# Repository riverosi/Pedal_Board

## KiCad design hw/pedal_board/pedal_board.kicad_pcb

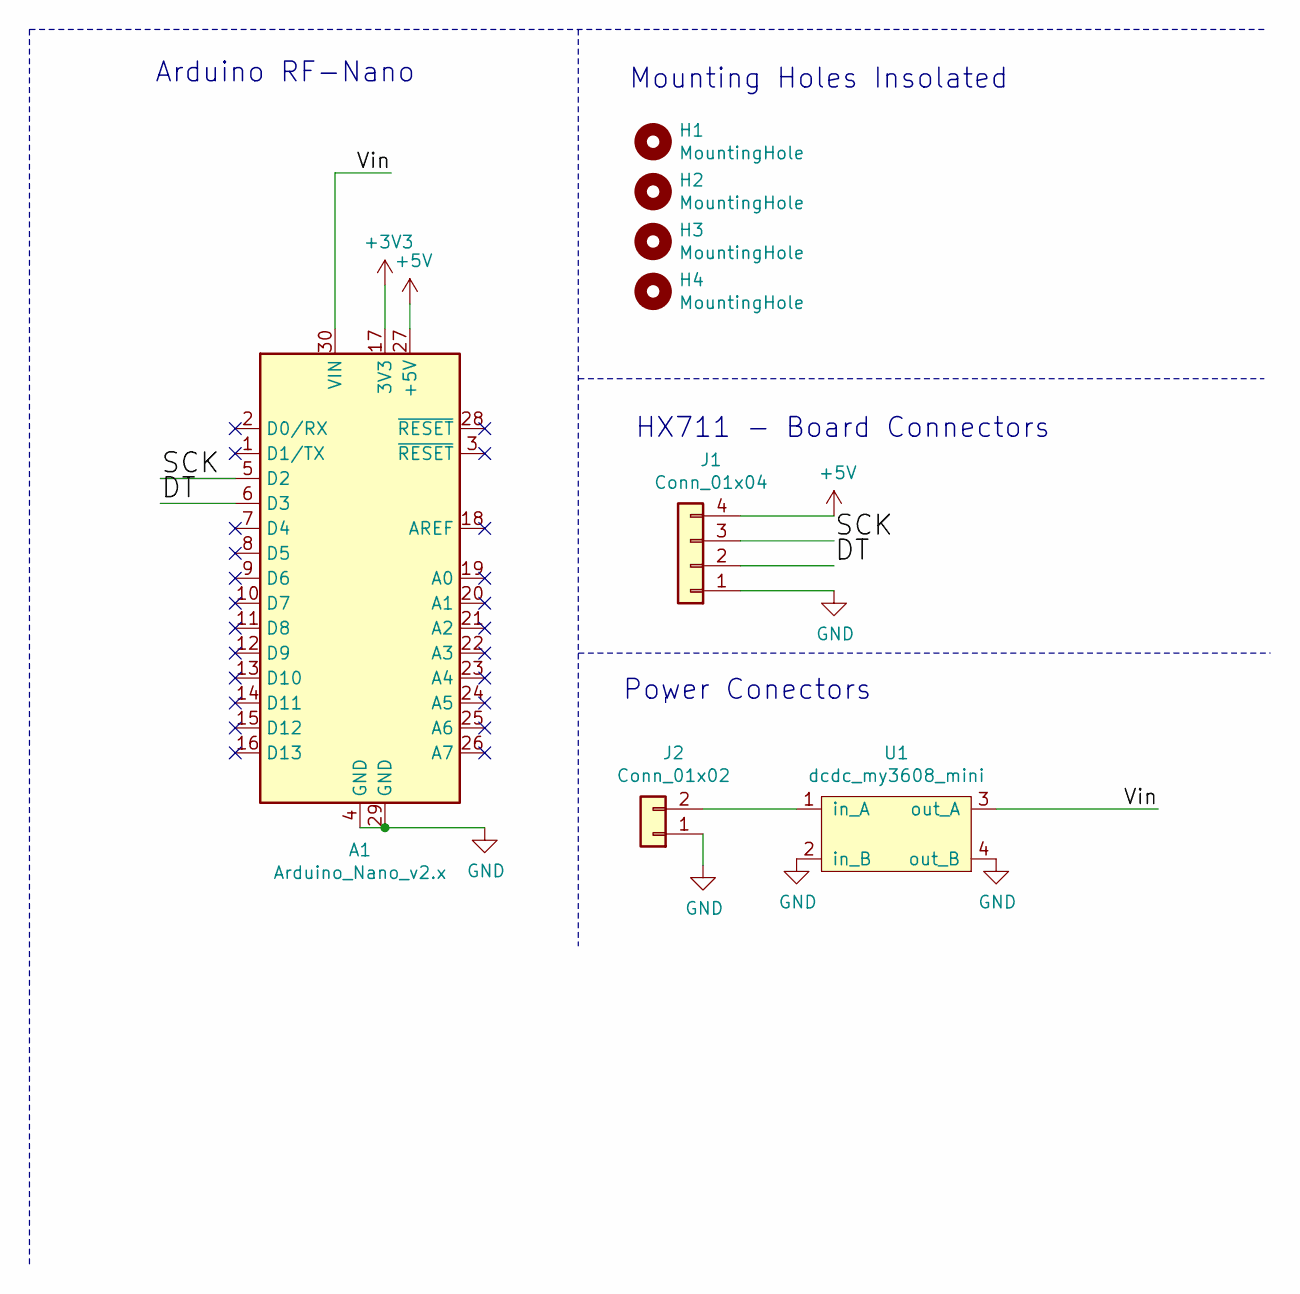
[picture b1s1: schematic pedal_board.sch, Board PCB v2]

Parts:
A1: Arduino_Nano_v2.x; Arduino_Nano
H1, H2, H3, H4: MountingHole; MountingHole_3.2mm_M3_Pad_Via
J1: Conn_01x04; HX711
J2: Conn_01x02; JST_XH_B2B-XH-A_1x02_P2.50mm_Vertical
U1: dcdc_my3608_mini; dcdc_module_mini

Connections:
+3V3: A1.17 (3V3)
+5V: A1.27 (+5V), J1.4
/DT: A1.6 (D3), J1.2
/SCK: A1.5 (D2), J1.3
/Vin: A1.30 (VIN), U1.3 (out_A)
GND: A1.4 (GND), A1.29 (GND), J1.1, J2.1, U1.2 (in_B), U1.4 (out_B)
unnamed: J2.2, U1.1 (in_A)

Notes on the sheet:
Mounting Holes Insolated
HX711 - Board Connectors
Power Conectors
Arduino RF-Nano

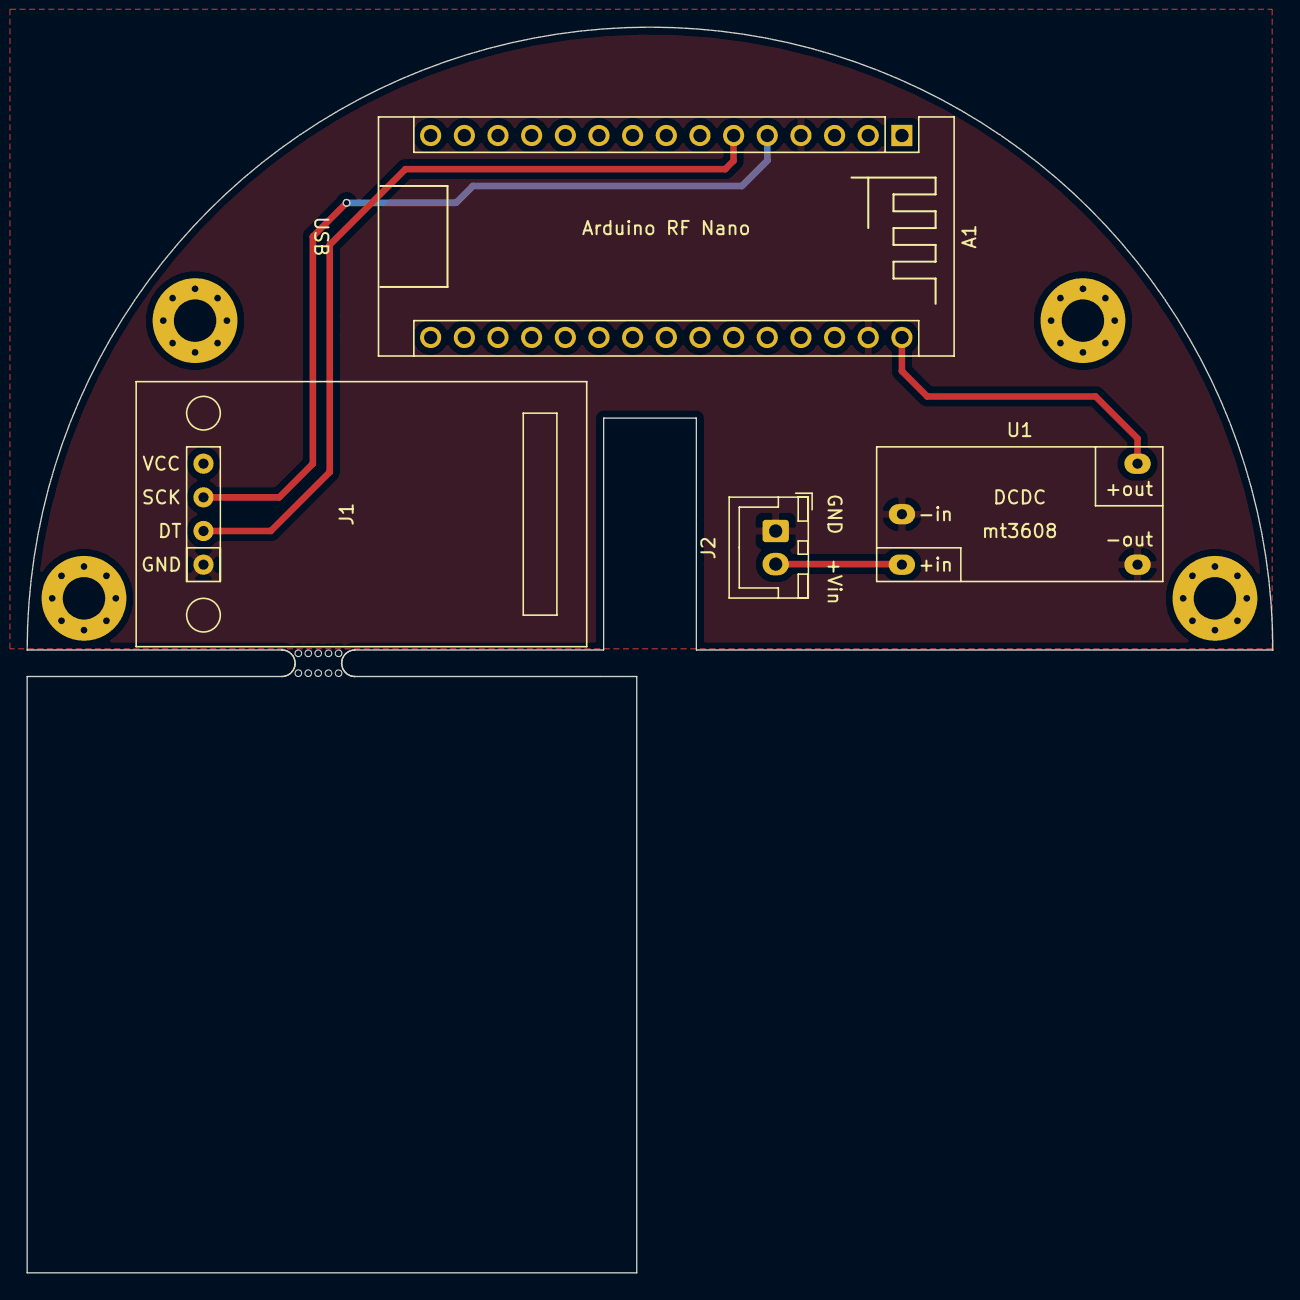
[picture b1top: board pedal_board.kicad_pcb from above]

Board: 2 copper layers, 94.0 x 94.0 mm, 9 parts (0 on the bottom side), 6 nets.

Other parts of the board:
mouse-bite-3mm-slot: VAL**; mouse-bite-3mm-slot

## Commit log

2021-02-21 Add Docs
2021-03-02 Add kicad files in hardware
2021-03-02 Add files of pedal_board v2
2021-03-08 Add Panelization test
2021-03-10 Add 3d models, send to review pcb
    review the 3d model of hx711
2021-03-17 Test panelization
2021-03-28 Added dcdc in board
